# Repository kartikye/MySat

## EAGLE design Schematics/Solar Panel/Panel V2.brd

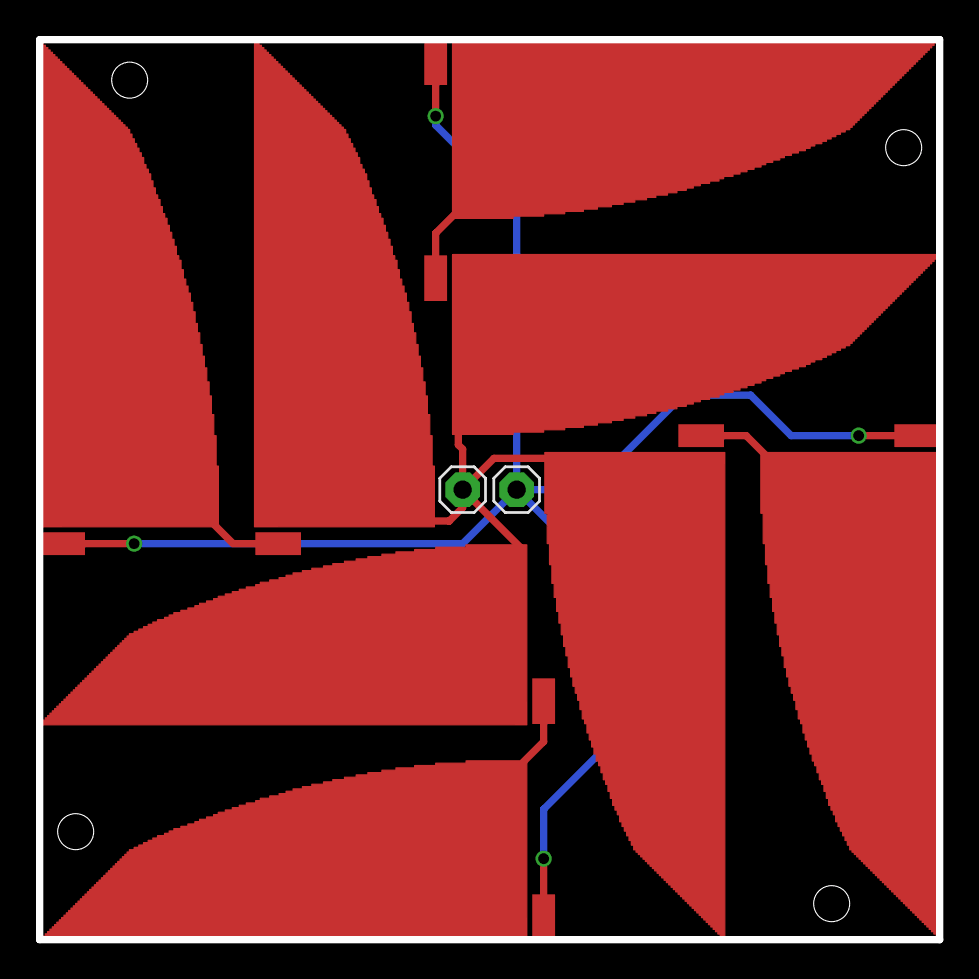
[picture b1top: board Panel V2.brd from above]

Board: 2 copper layers, 50.0 x 50.0 mm, 18 parts (0 on the bottom side), 6 nets.

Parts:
E$1, E$2, E$3, E$4, E$5, E$6, E$7, E$8: TRISOLX
E$9, E$10: 1X01
E$11, E$12, E$13, E$14, E$15, E$16, E$17, E$18: SMD1,27-2,54

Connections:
S$1: E$1.P$1, E$12.1
S$2: E$3.P$1, E$14.1
S$3: E$2.P$1, E$4.P$1, E$6.P$1, E$8.P$1, E$9.1
S$4: E$5.P$1, E$15.1
S$5: E$7.P$1, E$17.1
S$6: E$10.1, E$11.1, E$13.1, E$16.1, E$18.1
